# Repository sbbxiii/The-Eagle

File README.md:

# The Eagle: Custom STM32F405 Autonomous Flight Controller

[-orange.svg)](https://www.st.com/en/microcontrollers-microprocessors/stm32f405-415.html)

**The Eagle** is a custom, 4-layer high-reliability avionics flight controller (FC) designed around the **STMicroelectronics STM32F405RGT6** microcontroller. Engineered for autonomous Unmanned Aerial Vehicles (UAVs) and high-performance robotics platforms, the board integrates high-bandwidth IMU telemetry, multi-stage power conditioning, blackbox high-rate logging, and deterministic motor signaling into a **40.0 × 40.0 mm** board footprint with a **34.0 × 34.0 mm** mounting hole pattern.

---

## 3D Isometric View

---

## Hardware Gallery & Subsystems

| Top View (Components & Silicon) | Bottom View (Power Stages & Silkscreen) |
| :---: | :---: |
|  |  |
| *MCU, IMU, Baro, Flash, SWD, and I/O headers* | *Buck Regulator, LDO, TVS Diode, Reverse-Polarity FET, ESC pads* |

---

## Engineering Highlights & Key Specifications

### 1. Compute & Core Architecture
* **Primary MCU:** STM32F405RGT6 (ARM Cortex-M4 with single-precision FPU, 168 MHz core clock, 1 MB Flash, 192 KB SRAM).
* **Clocking:** External 8.000 MHz crystal oscillator feeding the internal PLL for zero-jitter core timing and USB 48 MHz generation.
* **Programming & Debug:** Onboard 4-pin SWD header (`3V3`, `SWDIO`, `SWCLK`, `GND`) for ST-Link / J-Link debugging and automated CI flashing.
* **Boot Management:** Hardware `BOOT` and `RST` tactile buttons supporting USB DFU system recovery.

### 2. Sensor Suite & Signal Integrity
* **Primary IMU:** **TDK InvenSense ICM-42688-P** 6-axis MEMS gyroscope/accelerometer on a dedicated high-speed **SPI1** bus (up to 20 MHz).
* **Interrupt Routing:** Dedicated hardware `EXTI` Data-Ready (`DRDY`) interrupt line tied directly to the MCU NVIC for deterministic 8 kHz loop timing.
* **Barometric Altimeter:** **Bosch Sensortec BMP390** precision pressure sensor on **I2C1** for sub-meter altitude hold.
* **Blackbox Storage:** **Winbond W25Q128JVSSIQ** (128 Mbit / 16 MB) SPI NOR Flash on **SPI3** for high-rate loop and telemetry logging.
* **Bus Isolation:** SPI and I2C signal traces are referenced directly to an unbroken Layer 2 Ground Plane to suppress crosstalk and high-frequency noise.

### 3. Power Distribution Network (PDN)
* **Battery Input:** 3S–6S LiPo input (9.0V to 26.0V nominal; rated up to 36V transient tolerance).
* **Transient Voltage Suppression (TVS):** Onboard **SMBJ28A** high-energy TVS clamp at the main battery junction to suppress motor inductive voltage spikes.
* **Reverse Polarity Protection:** P-channel MOSFET gate protection preventing accidental battery reverse-connection damage.
* **Synchronous Buck Converter:** Texas Instruments **LMR51430** step-down regulator delivering clean 5.0V @ 3.0A for receivers, telemetry, and peripheral rails.
* **Ultra-Low-Noise Sensor LDO:** Texas Instruments **TLV75733PDBV** (3.3V @ 1.0A) high-PSRR linear regulator exclusively isolating the analog sensors and MCU core.
* **Analog Telemetry:** Low-pass RC filtered 11:1 voltage divider (`VBAT_SENSE`) and ESC analog current input (`CURR_SENSE`).
* **USB Interface:** Micro-USB / USB-C pads protected by ST **USBLC6-2SC6** ultra-low capacitance bidirectional ESD suppressor.

---

## Silicon Registry & Pin Allocation Matrix

| Pin | Function | Peripheral Bus | Alternate Function | Purpose / Notes |
| :--- | :--- | :--- | :--- | :--- |
| **PA0** | `CURR_SENSE` | ADC1 | `ADC1_IN0` | Analog current sensing from ESC |
| **PA1** | `VBAT_SENSE` | ADC1 | `ADC1_IN1` | 11:1 voltage divider battery monitor |
| **PA4** | `IMU_CS` | GPIO | Output | Active-Low SPI Chip Select (ICM-42688-P) |
| **PA5** | `IMU_SCK` | SPI1 | `SPI1_SCK` | High-speed IMU clock (up to 20 MHz) |
| **PA6** | `IMU_MISO` | SPI1 | `SPI1_MISO` | IMU Master In / Slave Out |
| **PA7** | `IMU_MOSI` | SPI1 | `SPI1_MOSI` | IMU Master Out / Slave In |
| **PB0** | `MOTOR_1` | TIM3 | `TIM3_CH3` | Motor 1 output (DShot300/600 / PWM with DMA) |
| **PB1** | `MOTOR_2` | TIM3 | `TIM3_CH4` | Motor 2 output (DShot300/600 / PWM with DMA) |
| **PB4** | `MOTOR_3` | TIM3 | `TIM3_CH1` | Motor 3 output (DShot300/600 / PWM with DMA) |
| **PB5** | `MOTOR_4` | TIM3 | `TIM3_CH2` | Motor 4 output (DShot300/600 / PWM with DMA) |
| **PB6** | `I2C1_SCL` | I2C1 | `I2C1_SCL` | Barometer (BMP390) & External Magnetometer |
| **PB7** | `I2C1_SDA` | I2C1 | `I2C1_SDA` | Barometer (BMP390) & External Magnetometer |
| **PB10** | `UART3_TX` | USART3 | `USART3_TX` | ESC Telemetry / Auxiliary Serial |
| **PB11** | `UART3_RX` | USART3 | `USART3_RX` | ESC Telemetry / Auxiliary Serial |
| **PA9** | `UART1_TX` | USART1 | `USART1_TX` | High-speed Telemetry / Radio Control link |
| **PA10** | `UART1_RX` | USART1 | `USART1_RX` | High-speed Telemetry / Radio Control link |
| **PA2** | `UART2_TX` | USART2 | `USART2_TX` | GPS Receiver (UBX / NMEA protocol) |
| **PA3** | `UART2_RX` | USART2 | `USART2_RX` | GPS Receiver (UBX / NMEA protocol) |
| **PC10** | `FLASH_SCK` | SPI3 | `SPI3_SCK` | Blackbox Flash Clock |
| **PC11** | `FLASH_MISO`| SPI3 | `SPI3_MISO`| Blackbox Flash Data Out |
| **PC12** | `FLASH_MOSI`| SPI3 | `SPI3_MOSI`| Blackbox Flash Data In |
| **PD2** | `FLASH_CS` | GPIO | Output | Blackbox Flash Chip Select (W25Q128) |
| **PA11** | `USB_DM` | USB OTG FS | `OTG_FS_DM` | USB D- with ESD Clamping |
| **PA12** | `USB_DP` | USB OTG FS | `OTG_FS_DP` | USB D+ with ESD Clamping |
| **PA13** | `SWDIO` | SWD | `SWDIO` | Serial Wire Debug Data |
| **PA14** | `SWCLK` | SWD | `SWCLK` | Serial Wire Debug Clock |

---

## PCB Stackup & Fabrication Rules

* **Dimensions:** 40.00 mm × 40.00 mm outer footprint
* **Mounting Pattern:** 34.00 mm × 34.00 mm grid (M2 mounting pads)
* **Layer Count:** 4 Layers (Standard 1.6 mm FR-4 Stackup):
  * **Layer 1 (Top):** Component placement & High-Speed Signal routing
  * **Layer 2 (Inner 1):** Solid Ground Plane (GND) for low return-loop inductance
  * **Layer 3 (Inner 2):** Power Plane split (5.0V / 3.3V power distribution)
  * **Layer 4 (Bottom):** Power Switching Stages, ESC pads, and secondary signal traces
* **Minimum Trace / Space:** 0.15 mm / 0.15 mm (6 mil / 6 mil)
* **Minimum Drill:** 0.3 mm (via size: 0.6 mm outer diameter)
* **Design Rule Check (DRC):** **0 Errors, 0 Unconnected Nets**

---

## Project Deliverables & Design Assets

All design, firmware, and mechanical assets are included directly in this repository:

* 📄 **Schematic (PDF):** [`docs/AeroHawk_FC_Schematic_Rev1.1.pdf`](docs/AeroHawk_FC_Schematic_Rev1.1.pdf)
* 🛡️ **Flight Enclosure (STEP):** [`cad/Eagle_Case.step`](cad/Eagle_Case.step)
* 💻 **KiCad Source Files:** Located in [`hardware/`](hardware/) (`AeroHawk_FC.kicad_sch`, `AeroHawk_FC.kicad_pcb`, `AeroHawk_FC.step`)
* ⚡ **Firmware Port & Binaries:** Located in [`firmware/`](firmware/) (ArduPilot ChibiOS port & hardware blinky test)
* 🔍 **Hardware Audit & Verification:** [`docs/HARDWARE_REVISION_1.1_AUDIT.md`](docs/HARDWARE_REVISION_1.1_AUDIT.md)

---

## Firmware Support & Flashing

The hardware layout and pin allocation strictly adhere to the STM32 timer and peripheral mapping required by standard flight controller firmware:

1. **ArduPilot (ArduCopter ChibiOS):** Full custom board port located in [`firmware/ardupilot/`](firmware/ardupilot/) with pre-compiled `arducopter.bin` / `arducopter.hex` and `hwdef.dat` definition. Compatible with QGroundControl via native USB CDC or external telemetry.
2. **Hardware Bring-up & Diagnostics:** Low-level register blinky test in [`firmware/blinky_test/`](firmware/blinky_test/) to verify core clocking and the `PC8` status LED.
3. **Betaflight / INAV:** Compatible using STM32F405 target configuration with DShot DMA timer assignment.
4. **Custom Bare-Metal C++ / MATLAB Simulink:** Direct code generation via Embedded Coder / HAL drivers using the onboard SWD debug interface.

---

## How to Open in KiCad

1. Clone this repository:
   ```bash
   git clone https://github.com/sbbxiii/The-Eagle.git
   cd The-Eagle/hardware
   ```
2. Open `AeroHawk_FC.kicad_pro` using **KiCad 8.0 or newer** (tested on KiCad 10.0).
3. View schematics in `Eeschema` or board layout in `Pcbnew`.

---

## Author & License

Designed by **Osakwe Nmesoma Chukwukadibia, Bsc Engineering Student University of Debrecen**.

Licensed under the [MIT License](LICENSE).

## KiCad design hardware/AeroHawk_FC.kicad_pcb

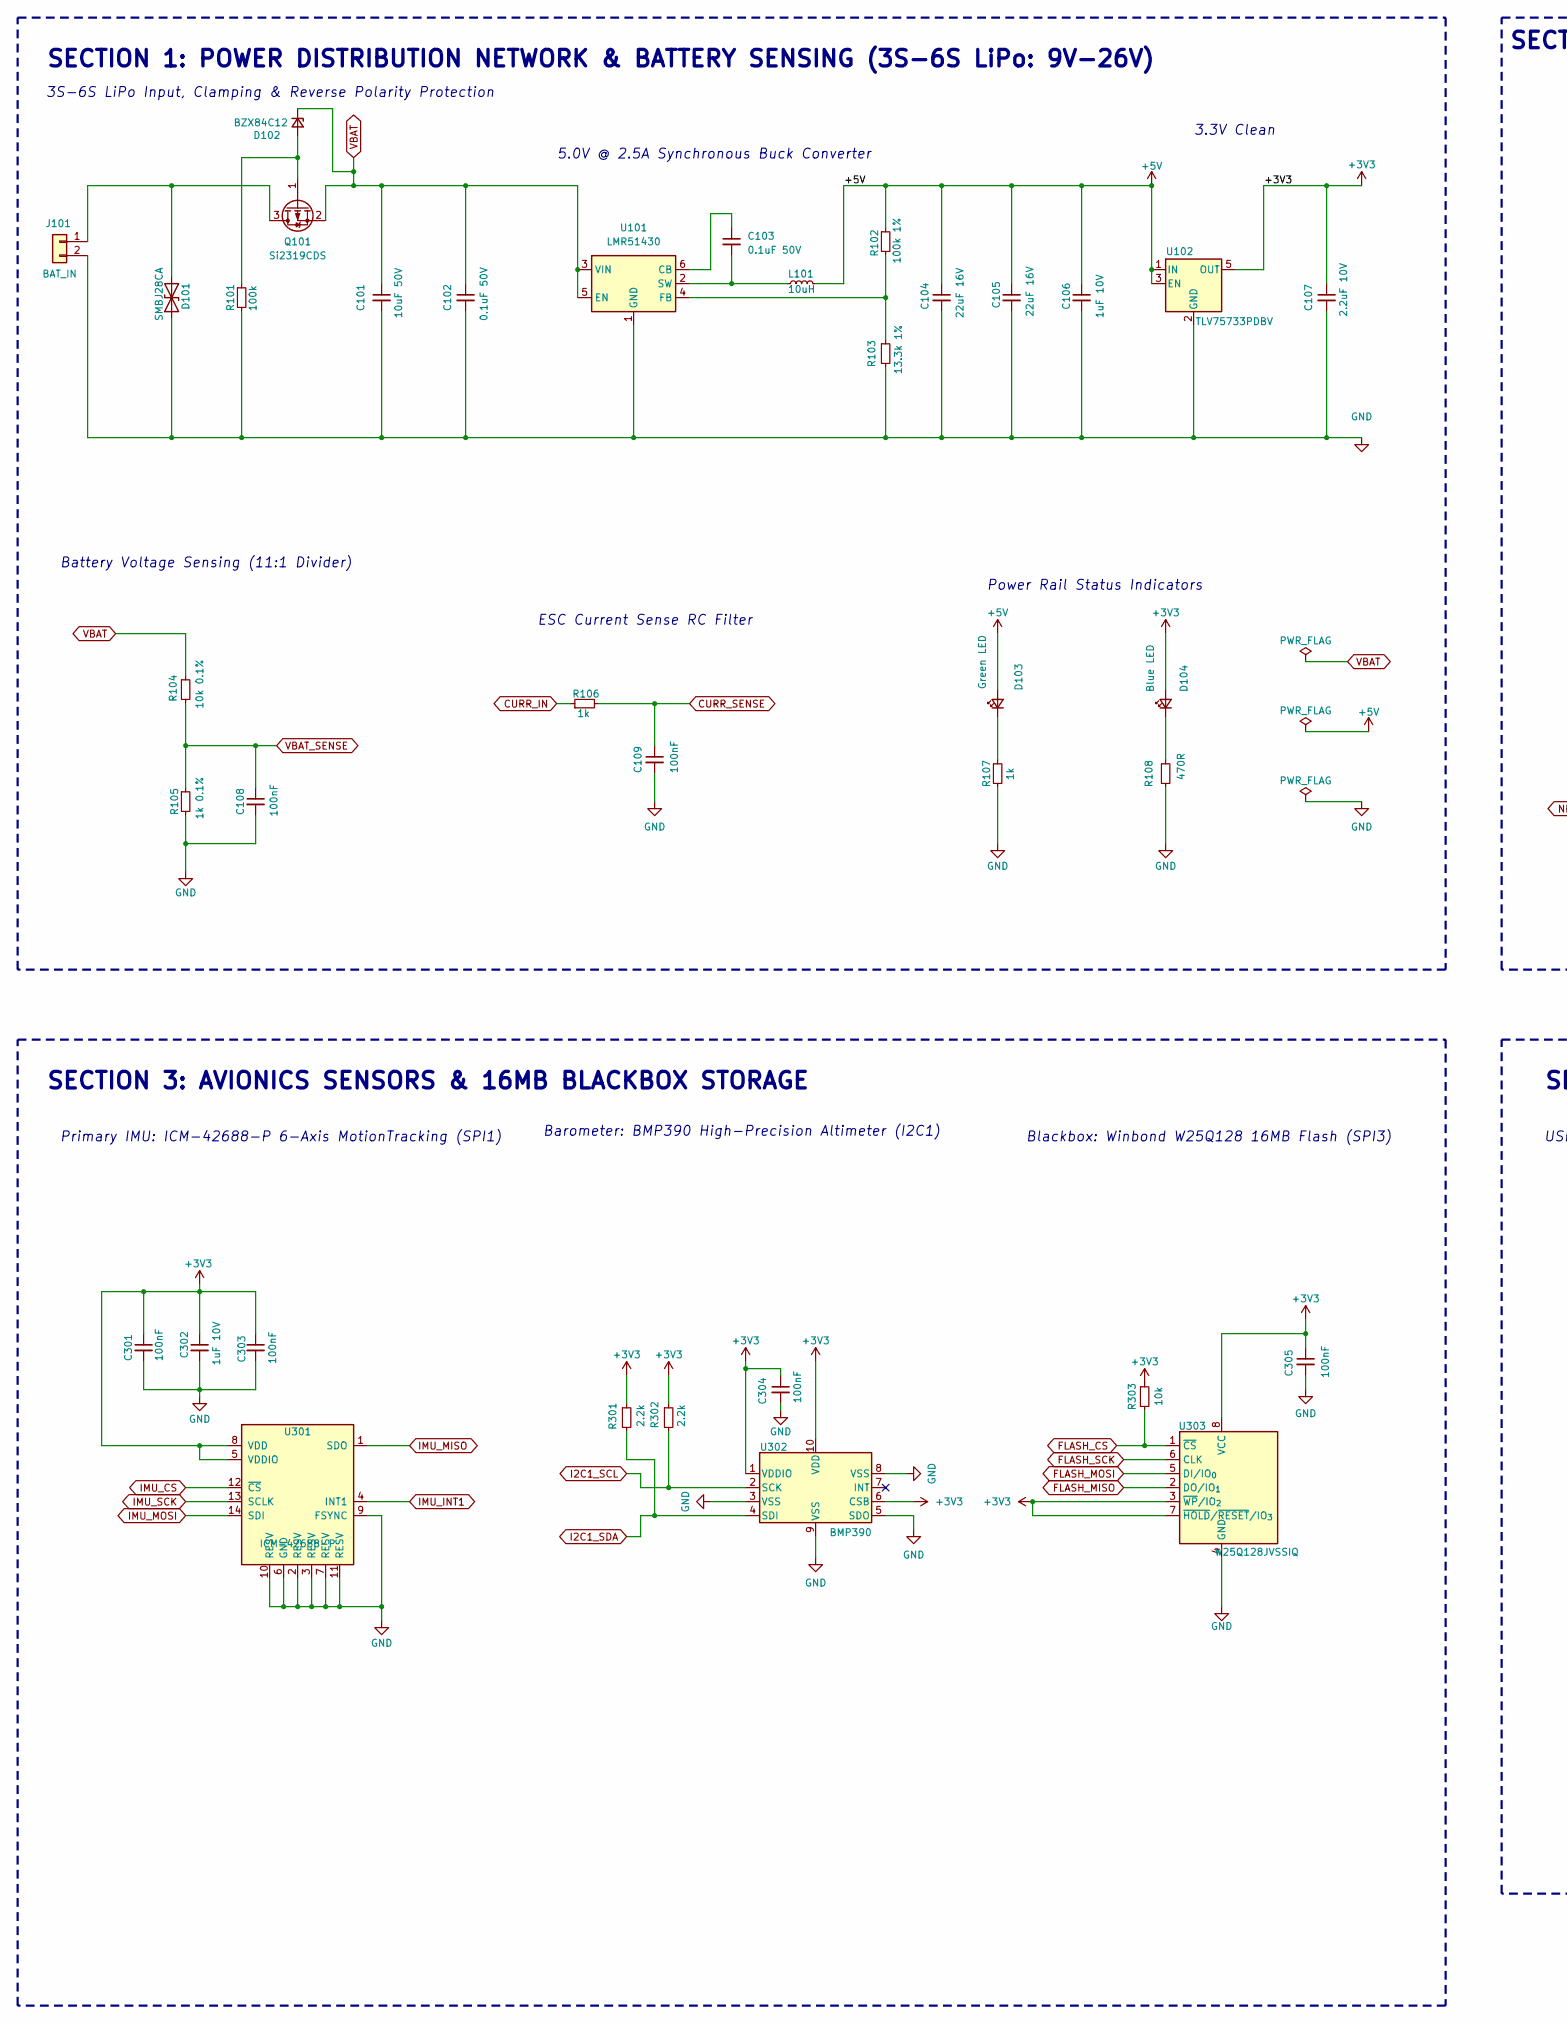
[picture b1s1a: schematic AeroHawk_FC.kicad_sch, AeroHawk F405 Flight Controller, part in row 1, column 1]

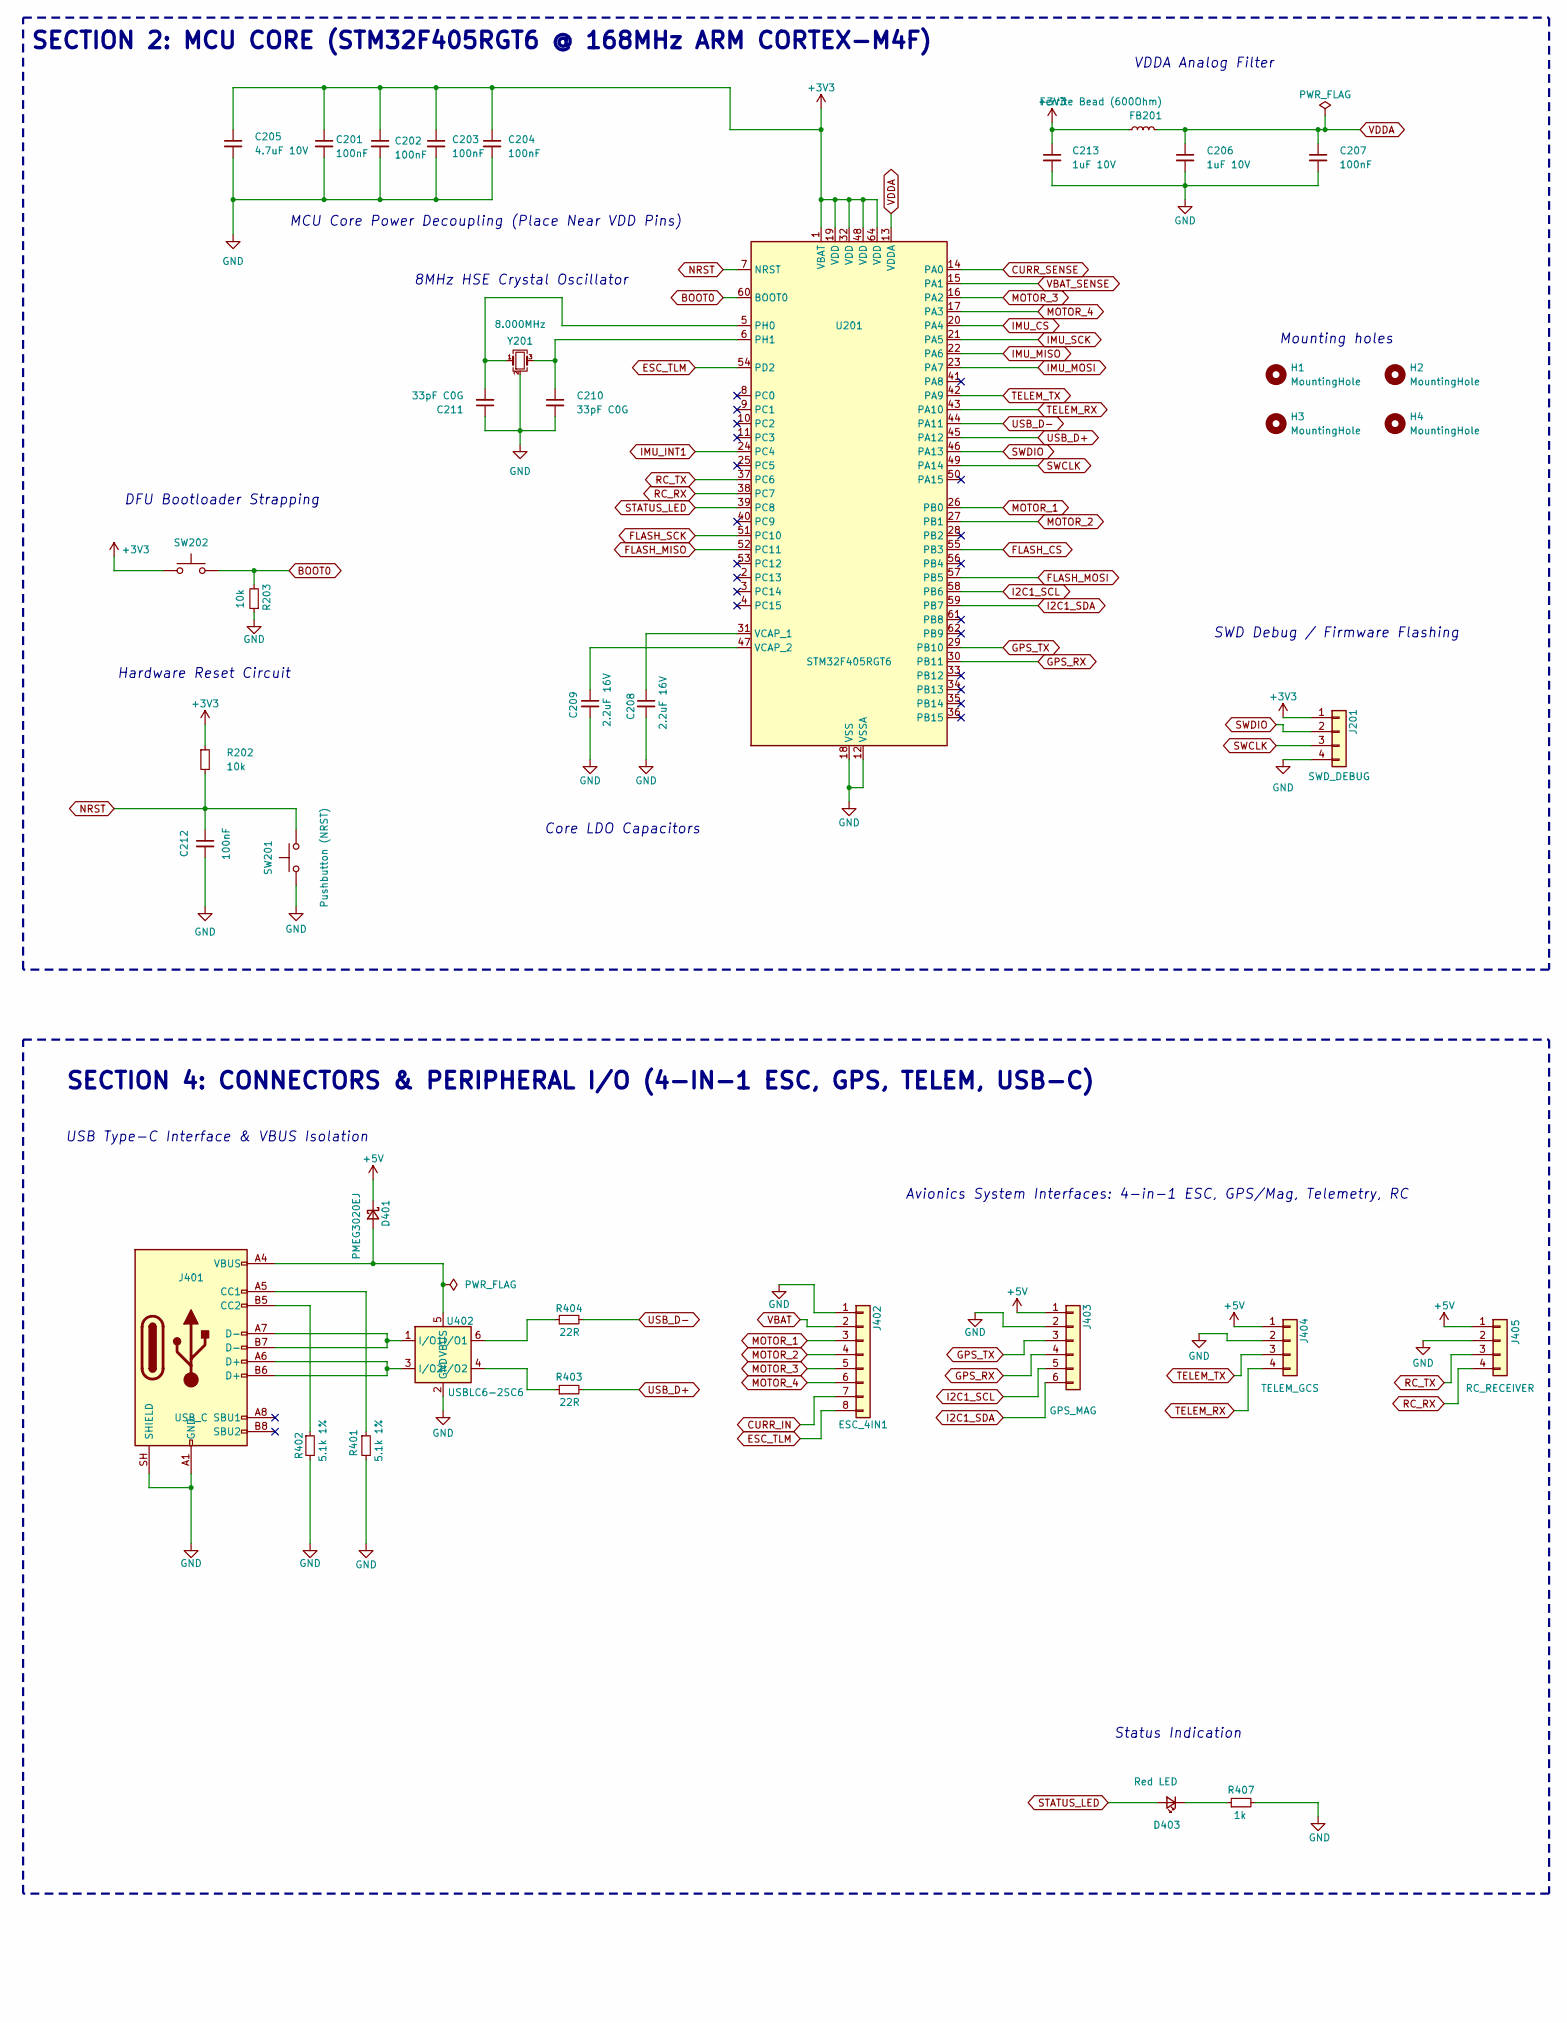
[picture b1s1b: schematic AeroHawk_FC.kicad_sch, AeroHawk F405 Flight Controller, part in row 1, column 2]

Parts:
C101: 10uF 50V; C_1206_3216Metric; MPN CL31B106KBHNNNE
C102, C103: 0.1uF 50V; C_0603_1608Metric; MPN CC0603KRX7R9BB104
C104, C105: 22uF 16V; C_1206_3216Metric; MPN CL21A226MPCLRNC
C106, C206, C213, C302: 1uF 10V; C_0603_1608Metric; MPN CC0603KRX7R7BB105
C107: 2.2uF 10V; C_0603_1608Metric; MPN CC0603KRX7R7BB225
C108, C109, C201, C202, C203, C204, C207, C212, C301, C303, C304, C305: 100nF; C_0603_1608Metric; MPN CC0603KRX7R9BB104
C205: 4.7uF 10V; C_0603_1608Metric; MPN CL10A475KP8NNNC
C208, C209: 2.2uF 16V; C_0603_1608Metric; MPN CC0603KRX7R7BB225
C210, C211: 33pF C0G; C_0603_1608Metric; MPN CC0603JRNPO9BN330
D101: SMBJ28CA; D_SMB; MPN SMBJ28CA
D102: BZX84C12; SOT-23; MPN BZX84C12
D103: Green LED; LED_0603_1608Metric; MPN 19-217/GHC-YR1S2/3T
D104: Blue LED; LED_0603_1608Metric; MPN 19-217/BHC-AP1Q2/3T
D401: PMEG3020EJ; D_SOD-323F; MPN PMEG3020EJ
D403: Red LED; LED_0603_1608Metric; MPN 19-217/R6C-AL1M2VY/3T
FB201: Ferrite Bead (600Ohm); L_0603_1608Metric; MPN BLM18PG121SN1D
H1, H2, H3, H4: MountingHole; MountingHole_2.2mm_M2_Pad
J101: BAT_IN; PinHeader_1x02_P2.54mm_Vertical; MPN 22-23-2021
J201: SWD_DEBUG; PinHeader_1x04_P1.27mm_Vertical; MPN M50-3530442
J401: USB_C; USB_C_Receptacle_HRO_TYPE-C-31-M-12; MPN TYPE-C-31-M-12
J402: ESC_4IN1; JST_SH_SM08B-SRSS-TB_1x08-1MP_P1.00mm_Horizontal; MPN SM08B-SRSS-TB
J403: GPS_MAG; JST_SH_SM06B-SRSS-TB_1x06-1MP_P1.00mm_Horizontal; MPN SM06B-SRSS-TB
J404: TELEM_GCS; JST_SH_SM04B-SRSS-TB_1x04-1MP_P1.00mm_Horizontal; MPN SM04B-SRSS-TB
J405: RC_RECEIVER; JST_SH_SM04B-SRSS-TB_1x04-1MP_P1.00mm_Horizontal; MPN SM04B-SRSS-TB
L101: 10uH; L_Wurth_WE-LQSH-4020; MPN 74405042100
Q101: Si2319CDS; SOT-23; MPN Si2319CDS-T1-GE3
R101: 100k; R_0603_1608Metric; MPN RC0603FR-07100KL
R102: 100k 1%; R_0603_1608Metric; MPN RC0603FR-07100KL
R103: 13.3k 1%; R_0603_1608Metric; MPN RC0603FR-0713K3L
R104: 10k 0.1%; R_0603_1608Metric; MPN RT0603BRD0710KL
R105: 1k 0.1%; R_0603_1608Metric; MPN RT0603BRD071KL
R106, R107, R407: 1k; R_0603_1608Metric; MPN RC0603FR-071KL
R108: 470R; R_0603_1608Metric; MPN RC0603FR-07470RL
R202, R203, R303: 10k; R_0603_1608Metric; MPN RC0603FR-0710KL
R301, R302: 2.2k; R_0603_1608Metric; MPN RC0603FR-072K2L
R401, R402: 5.1k 1%; R_0603_1608Metric; MPN RC0603FR-075K1L
R403, R404: 22R; R_0603_1608Metric; MPN RC0603FR-0722RL
SW201: Pushbutton (NRST); SW_Push_SPST_NO_PTS810; MPN PTS810SJM250SMTRLFS
SW202: Pushbutton (BOOT0); SW_Push_SPST_NO_PTS810; MPN PTS810SJM250SMTRLFS
U101: LMR51430; SOT-23-6; MPN LMR51430XDDCR
U102: TLV75733PDBV; SOT-23-5; MPN TLV75733PDBVR
U201: STM32F405RGT6; LQFP-64_10x10mm_P0.5mm; MPN STM32F405RGT6
U301: ICM-42688-P; InvenSense_LGA-14_2.5x3mm_P0.5mm; MPN ICM-42688-P
U302: BMP390; Bosch_LGA-10_2x2mm_P0.5mm; MPN BMP390
U303: W25Q128JVSSIQ; SOIC-8_5.23x5.23mm_P1.27mm; MPN W25Q128JVSIQ
U402: USBLC6-2SC6; SOT-23-6; MPN USBLC6-2SC6
Y201: 8.000MHz; Crystal_SMD_3225-4Pin_3.2x2.5mm; MPN X32258MSB4SI

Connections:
+3V3: C107.1, C201.1, C202.1, C203.1, C204.1, C205.1, C213.1, C301.1, C302.1, C303.1, C304.1, C305.1, D104.2 (A), FB201.1, J201.1, R202.1, R301.1, R302.1, R303.1, SW202.1, U102.5 (OUT), U201.1 (VBAT), U201.19 (VDD), U201.32 (VDD), U201.48 (VDD), U201.64 (VDD), U301.5 (VDDIO), U301.8 (VDD), U302.1 (VDDIO), U302.6 (CSB), U302.10 (VDD), U303.3 (~WP/IO_{2}), U303.7 (~HOLD/~RESET/IO_{3}), U303.8 (VCC)
BOOT0: R203.2, SW202.2, U201.60 (BOOT0)
CURR_IN: J402.7, R106.1
CURR_SENSE: C109.1, R106.2, U201.14 (PA0)
ESC_TLM: J402.8, U201.54 (PD2)
FLASH_CS: R303.2, U201.55 (PB3), U303.1 (~CS)
FLASH_MISO: U201.52 (PC11), U303.2 (DO/IO_{1})
FLASH_MOSI: U201.57 (PB5), U303.5 (DI/IO_{0})
FLASH_SCK: U201.51 (PC10), U303.6 (CLK)
GPS_RX: J403.4, U201.30 (PB11)
GPS_TX: J403.3, U201.29 (PB10)
I2C1_SCL: J403.5, R302.2, U201.58 (PB6), U302.2 (SCK)
I2C1_SDA: J403.6, R301.2, U201.59 (PB7), U302.4 (SDI)
IMU_CS: U201.20 (PA4), U301.12 (~CS)
IMU_INT1: U201.24 (PC4), U301.4 (INT1)
IMU_MISO: U201.22 (PA6), U301.1 (SDO)
IMU_MOSI: U201.23 (PA7), U301.14 (SDI)
IMU_SCK: U201.21 (PA5), U301.13 (SCLK)
MOTOR_1: J402.3, U201.26 (PB0)
MOTOR_2: J402.4, U201.27 (PB1)
MOTOR_3: J402.5, U201.16 (PA2)
MOTOR_4: J402.6, U201.17 (PA3)
NRST: C212.1, R202.2, SW201.2, U201.7 (NRST)
unnamed: D101.2 (A2), J101.1, Q101.3 (D)
unnamed: D102.2 (A), Q101.1 (G), R101.1
unnamed: D103.1 (K), R107.1
unnamed: D104.1 (K), R108.1
unnamed: D403.1 (K), R407.1
unnamed: J401.A5 (CC1), R401.1
unnamed: J401.B5 (CC2), R402.1
unnamed: J401.A6 (D+), J401.B6 (D+), U402.3 (I/O2)
unnamed: J401.A7 (D-), J401.B7 (D-), U402.1 (I/O1)
unnamed: R403.1, U402.4 (I/O2)
unnamed: R404.1, U402.6 (I/O1)
unnamed: C103.1, U101.6 (CB)
unnamed: R102.2, R103.1, U101.4 (FB)
unnamed: C103.2, L101.1, U101.2 (SW)
unnamed: C211.2, U201.5 (PH0), Y201.1
unnamed: C210.1, U201.6 (PH1), Y201.3
unnamed: C208.1, U201.31 (VCAP_1)
unnamed: C209.1, U201.47 (VCAP_2)
RC_RX: J405.4, U201.38 (PC7)
RC_TX: J405.3, U201.37 (PC6)
STATUS_LED: D403.2 (A), U201.39 (PC8)
SWCLK: J201.3, U201.49 (PA14)
SWDIO: J201.2, U201.46 (PA13)
TELEM_RX: J404.4, U201.43 (PA10)
TELEM_TX: J404.3, U201.42 (PA9)
USB_D+: R403.2, U201.45 (PA12)
USB_D-: R404.2, U201.44 (PA11)
VBAT_SENSE: C108.1, R104.2, R105.1, U201.15 (PA1)

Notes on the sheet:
Blackbox: Winbond W25Q128 16MB Flash (SPI3)
Battery Voltage Sensing (11:1 Divider)
8MHz HSE Crystal Oscillator
SWD Debug / Firmware Flashing
Barometer: BMP390 High-Precision Altimeter (I2C1)
MCU Core Power Decoupling (Place Near VDD Pins)
SECTION 3: AVIONICS SENSORS & 16MB BLACKBOX STORAGE
USB Type-C Interface & VBUS Isolation
Power Rail Status Indicators
5.0V @ 2.5A Synchronous Buck Converter
Core LDO Capacitors
SECTION 2: MCU CORE (STM32F405RGT6 @ 168MHz ARM CORTEX-M4F)
3S-6S LiPo Input, Clamping & Reverse Polarity Protection
Mounting holes
Avionics System Interfaces: 4-in-1 ESC, GPS/Mag, Telemetry, RC
SECTION 1: POWER DISTRIBUTION NETWORK & BATTERY SENSING (3S-6S LiPo: 9V-26V)
Hardware Reset Circuit
3.3V Clean
SECTION 4: CONNECTORS & PERIPHERAL I/O (4-IN-1 ESC, GPS, TELEM, USB-C)
ESC Current Sense RC Filter
VDDA Analog Filter
DFU Bootloader Strapping
Primary IMU: ICM-42688-P 6-Axis MotionTracking (SPI1)
Status Indication

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
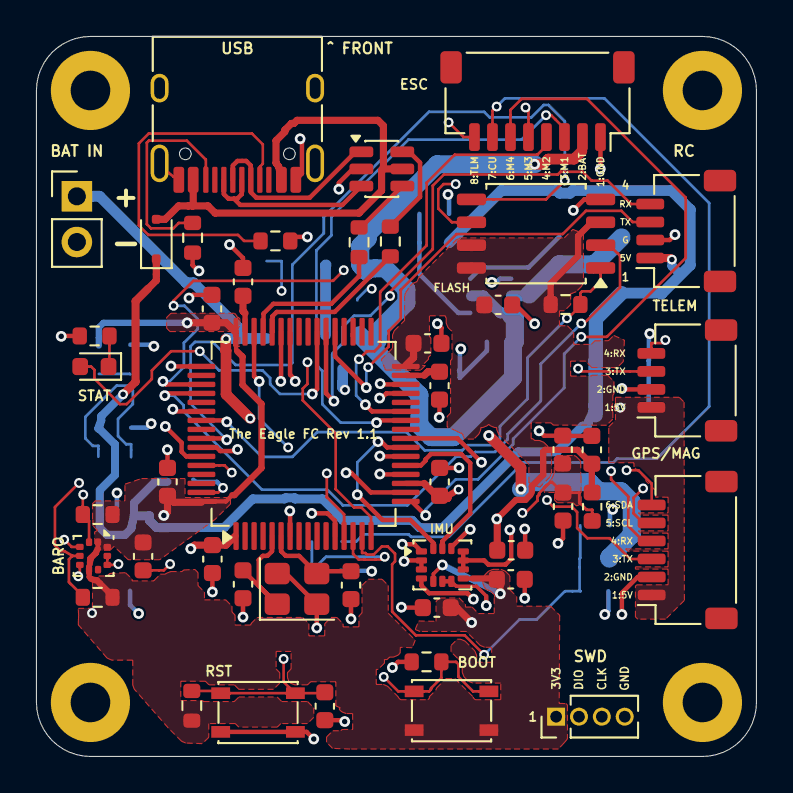
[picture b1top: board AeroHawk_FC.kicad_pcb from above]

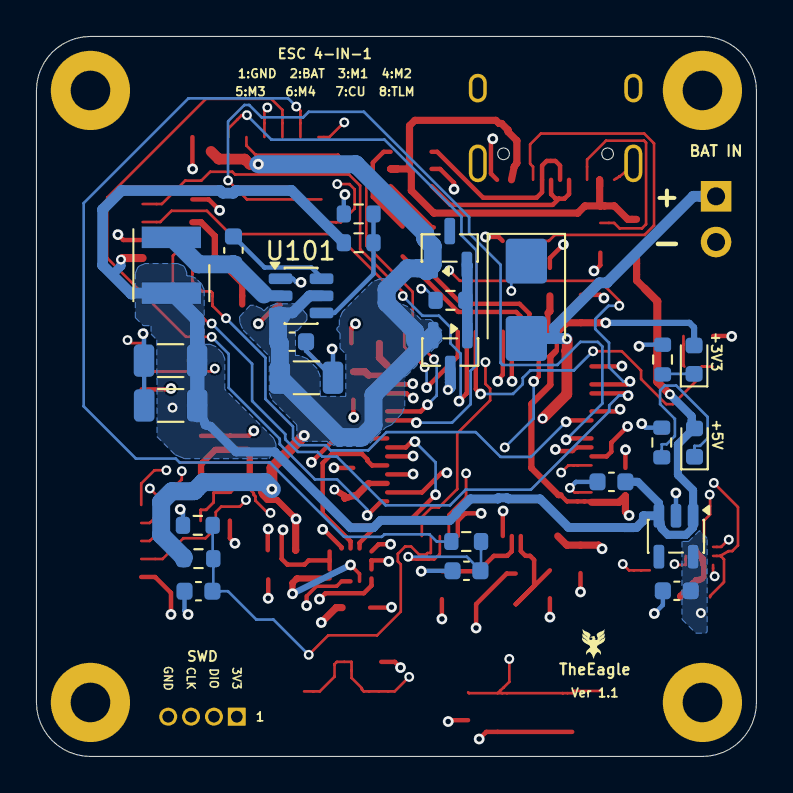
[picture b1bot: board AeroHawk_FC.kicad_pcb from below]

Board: 4 copper layers, 40.0 x 40.0 mm, 75 parts (25 on the bottom side), 56 nets.

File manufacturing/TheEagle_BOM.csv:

"Refs","Value","Footprint","Qty","DNP"
"C101","10uF 50V","Capacitor_SMD:C_1206_3216Metric","1",""
"C102","0.1uF 50V","Capacitor_SMD:C_0603_1608Metric","1",""
"C103","0.1uF 50V","Capacitor_SMD:C_0603_1608Metric","1",""
"C104","22uF 16V","Capacitor_SMD:C_1206_3216Metric","1",""
"C105","22uF 16V","Capacitor_SMD:C_1206_3216Metric","1",""
"C106","1uF 10V","Capacitor_SMD:C_0603_1608Metric","1",""
"C107","2.2uF 10V","Capacitor_SMD:C_0603_1608Metric","1",""
"C108","100nF","Capacitor_SMD:C_0603_1608Metric","1",""
"C109","100nF","Capacitor_SMD:C_0603_1608Metric","1",""
"C201","100nF","Capacitor_SMD:C_0603_1608Metric","1",""
"C202","100nF","Capacitor_SMD:C_0603_1608Metric","1",""
"C203","100nF","Capacitor_SMD:C_0603_1608Metric","1",""
"C204","100nF","Capacitor_SMD:C_0603_1608Metric","1",""
"C205","4.7uF 10V","Capacitor_SMD:C_0603_1608Metric","1",""
"C206","1uF 10V","Capacitor_SMD:C_0603_1608Metric","1",""
"C207","100nF","Capacitor_SMD:C_0603_1608Metric","1",""
"C208","2.2uF 16V","Capacitor_SMD:C_0603_1608Metric","1",""
"C209","2.2uF 16V","Capacitor_SMD:C_0603_1608Metric","1",""
"C210","33pF C0G","Capacitor_SMD:C_0603_1608Metric","1",""
"C211","33pF C0G","Capacitor_SMD:C_0603_1608Metric","1",""
"C212","100nF","Capacitor_SMD:C_0603_1608Metric","1",""
"C213","1uF 10V","Capacitor_SMD:C_0603_1608Metric","1",""
"C301","100nF","Capacitor_SMD:C_0603_1608Metric","1",""
"C302","1uF 10V","Capacitor_SMD:C_0603_1608Metric","1",""
"C303","100nF","Capacitor_SMD:C_0603_1608Metric","1",""
"C304","100nF","Capacitor_SMD:C_0603_1608Metric","1",""
"C305","100nF","Capacitor_SMD:C_0603_1608Metric","1",""
"D101","SMBJ28CA","Diode_SMD:D_SMB","1",""
"D102","BZX84C12","Package_TO_SOT_SMD:SOT-23","1",""
"D103","Green LED","LED_SMD:LED_0603_1608Metric","1",""
"D104","Blue LED","LED_SMD:LED_0603_1608Metric","1",""
"D401","PMEG3020EJ","Diode_SMD:D_SOD-323F","1",""
"D403","Red LED","LED_SMD:LED_0603_1608Metric","1",""
"FB201","Ferrite Bead (600Ω)","Inductor_SMD:L_0603_1608Metric","1",""
"J101","BAT_IN","Connector_PinHeader_2.54mm:PinHeader_1x02_P2.54mm_Vertical","1",""
"J201","SWD_DEBUG","Connector_PinHeader_1.27mm:PinHeader_1x04_P1.27mm_Vertical","1",""
"J401","USB_C","Connector_USB:USB_C_Receptacle_HRO_TYPE-C-31-M-12","1",""
"J402","ESC_4IN1","Connector_JST:JST_SH_SM08B-SRSS-TB_1x08-1MP_P1.00mm_Horizontal","1",""
"J403","GPS_MAG","Connector_JST:JST_SH_SM06B-SRSS-TB_1x06-1MP_P1.00mm_Horizontal","1",""
"J404","TELEM_GCS","Connector_JST:JST_SH_SM04B-SRSS-TB_1x04-1MP_P1.00mm_Horizontal","1",""
"J405","RC_RECEIVER","Connector_JST:JST_SH_SM04B-SRSS-TB_1x04-1MP_P1.00mm_Horizontal","1",""
"L101","10uH","Inductor_SMD_Wurth:L_Wurth_WE-LQSH-4020","1",""
"Q101","Si2319CDS","Package_TO_SOT_SMD:SOT-23","1",""
"R101","100k","Resistor_SMD:R_0603_1608Metric","1",""
"R102","100k 1%","Resistor_SMD:R_0603_1608Metric","1",""
"R103","13.3k 1%","Resistor_SMD:R_0603_1608Metric","1",""
"R104","10k 0.1%","Resistor_SMD:R_0603_1608Metric","1",""
"R105","1k 0.1%","Resistor_SMD:R_0603_1608Metric","1",""
"R106","1k","Resistor_SMD:R_0603_1608Metric","1",""
"R107","1k","Resistor_SMD:R_0603_1608Metric","1",""
"R108","470R","Resistor_SMD:R_0603_1608Metric","1",""
"R202","10k","Resistor_SMD:R_0603_1608Metric","1",""
"R203","10k","Resistor_SMD:R_0603_1608Metric","1",""
"R301","2.2k","Resistor_SMD:R_0603_1608Metric","1",""
"R302","2.2k","Resistor_SMD:R_0603_1608Metric","1",""
"R303","10k","Resistor_SMD:R_0603_1608Metric","1",""
"R401","5.1k 1%","Resistor_SMD:R_0603_1608Metric","1",""
"R402","5.1k 1%","Resistor_SMD:R_0603_1608Metric","1",""
"R403","22R","Resistor_SMD:R_0603_1608Metric","1",""
"R404","22R","Resistor_SMD:R_0603_1608Metric","1",""
"R407","1k","Resistor_SMD:R_0603_1608Metric","1",""
"SW201","Pushbutton (NRST)","Button_Switch_SMD:SW_Push_SPST_NO_PTS810","1",""
"SW202","Pushbutton (BOOT0)","Button_Switch_SMD:SW_Push_SPST_NO_PTS810","1",""
"U101","LMR51430","Package_TO_SOT_SMD:SOT-23-6","1",""
"U102","TLV75733PDBV","Package_TO_SOT_SMD:SOT-23-5","1",""
"U201","STM32F405RGT6","Package_QFP:LQFP-64_10x10mm_P0.5mm","1",""
"U301","ICM-42688-P","Package_LGA:InvenSense_LGA-14_2.5x3mm_P0.5mm","1",""
"U302","BMP390","Package_LGA:Bosch_LGA-10_2x2mm_P0.5mm","1",""
"U303","W25Q128JVSSIQ","Package_SO:SOIC-8_5.23x5.23mm_P1.27mm","1",""
"U402","USBLC6-2SC6","Package_TO_SOT_SMD:SOT-23-6","1",""
"Y201","8.000MHz","Crystal:Crystal_SMD_3225-4Pin_3.2x2.5mm","1",""

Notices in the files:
README.md:
License: MIT
